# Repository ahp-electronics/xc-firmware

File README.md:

# AHP XC Quantum correlators firmware 

#### This repository contains code of the XC series multichannel multi-order cross-correlators

You'll find board and device specific files into the boards/ folder, device files contain some custom parameters that can characterize the device:

```
parameter PLL_FREQUENCY = 400000000;	//The pll frequency
parameter CLK_FREQUENCY = 10000000;	//The crystal frequency
parameter SIN_FREQUENCY = 50;		//The internal optional PSU frequency
parameter MUX_LINES = 1;		//Muxer lines
parameter NUM_LINES = 8;		//Lines per each Muxer line
parameter DELAY_SIZE = 2048;		//If 4 use quadrature sampling, if 0 use single sample quadrature sampling, else the delay FIFO size
parameter LAG_CROSS = 1;		//Lag lines size for live crosscorrelation
parameter LAG_AUTO = 1;			//Lag lines size for live autocorrelation
parameter RESOLUTION = 24;		//Resolution (count capacity) of each correlation/intensity counter
parameter HAS_LEDS = 1;			//Has this device output lines? (power switches or indicator or ramp generators sync?)
parameter HAS_CROSSCORRELATOR = 1;	//Has this device crosscorrelation capability?
parameter HAS_PSU = 0;			//Has this device a software PSU?
parameter HAS_CUMULATIVE_ONLY = 0;	//Has this device not on-edge counting?
parameter BAUD_RATE = 2000000;		//Communication port baud rate
parameter WORD_WIDTH = 1;		//Word width (greater than 1 when using ADC - must be in sync with the ADC ramp gener
parameter BINARY = 0;		//use binary packet transmission instead of ASCII
parameter USE_UART = 1;			//Use UART or SPI communication?
parameter USE_SOFT_CLOCK = 1;			//Limit usage of gated clocks
parameter MAX_ORDER = 2;			//Maximum crosscorrelation order
```

The generated SVF file can be downloaded to the device using urJTAG http://urjtag.org/

The cross-platform driver library: https://github.com/ahp-electronics/libahp-xc

To use the correlator try the GUI: https://github.com/ahp-electronics/xc-gui

The project runs at 10MHz and uses 2 Mbaud/second UART communication with the host initially

Here below is defined the communication protocol:

    0x0d: Set integration parameters: bit 4 => enable capture, bit 5 => use external clock, bit 6 => reset timestamp when enabling capture, bit 7 => extra commands
    0x01: select active line: first byte: bits [7:4] => length of command LSN, second byte: length of command MSN, next bytes: bits [7:4] => active line LSN first
    0x02: led lines: extra commands => nibble indexer, bits [7:4] => power voltage value
    0x03: if extra commands = 1 first byte: bits [7:4] => length of command LSN, second byte: length of command MSN, next bytes: bits [7:4] => cross-correlator order LSN first, if extra commands = 0 baudrate 57600 left-shifted by bits [7:4] 
    0x04: Set voltage: extra commands => nibble indexer, bits [7:4] => power voltage value
    0x08: sampling clock tau =  first two byte: bits [7:4] => length of command LSN first, next bytes: bits [7:4] => value LSN first - if test[5:4] is 0 scan increment, if test[5:4] is 1 scan length if test[5:4] scan start channel if extra commands = 0 autocorrelator, if extra commands = 1 crosscorrelator.
    0x0c: Set tests: extra commands => nibble indexer, bits [7:4] => test lines value - bit 1 => enable autocorrelation scan, bit 2 => enable crosscorrelation scan, bit 3 => BCM encoder on led 0 (pulse XOR by sampling clock), bits [5:4] => indexer of sampling clock tau

The count of pulses and correlation comes with an ASCII packet string ended with a 0x0d character

Each packet starts with a header with payload length indication, it is possible to change some parameters from the code

header

    char 0: Nibble length of input lines hex digits [n0]
    chars +n0: hexadecimal inputs quantity
    char +1: Nibble length of sample size value hex digits [n1]
    chars +n1: hexadecimal sample size value
    char +1: Nibble length of delay channels hex digits [n2]
    chars +n2: hexadecimal delay channels
    char +1: Nibble length of live autocorrelator delay channels hex digits [n3]
    chars +n3: hexadecimal live autocorrelator delay channels
    char +1: Nibble length of live crosscorrelator delay channels hex digits [n4]
    chars +n4: hexadecimal live crosscorrelator delay channels
    chars +2 hexadecimal flags [bits: 0=live autocorrelator, 1=live crosscorrelator, 2=leds available, 3=cross-correlator, 4=Nyquist sampling, 5=Shannon sampling]
    chars +4: hexadecimal value of the clock tau in picoseconds

payload

    chars +lines*(sample size)#: pulses count of each line within the integration time
    chars +lines*2*(sample size)#: autocorrelations real/imaginary count of each line within the packet time
    chars +baselines*2*(sample size/4)#: crosscorrelations real/imaginary count of pulses of each line with others ones within the packet time
    chars +16: 8-byte timestamp of current packet

checksum

    chars +2: 1-byte CRC of packet payload

EOP

    chars +1: carriage return indicates end of packet

The packet time is determined by the baud rate and the packet size, the sampling rate is determined by the clock tau multiplied by the number of mux lines, raised by the clock tau power of two exponent.

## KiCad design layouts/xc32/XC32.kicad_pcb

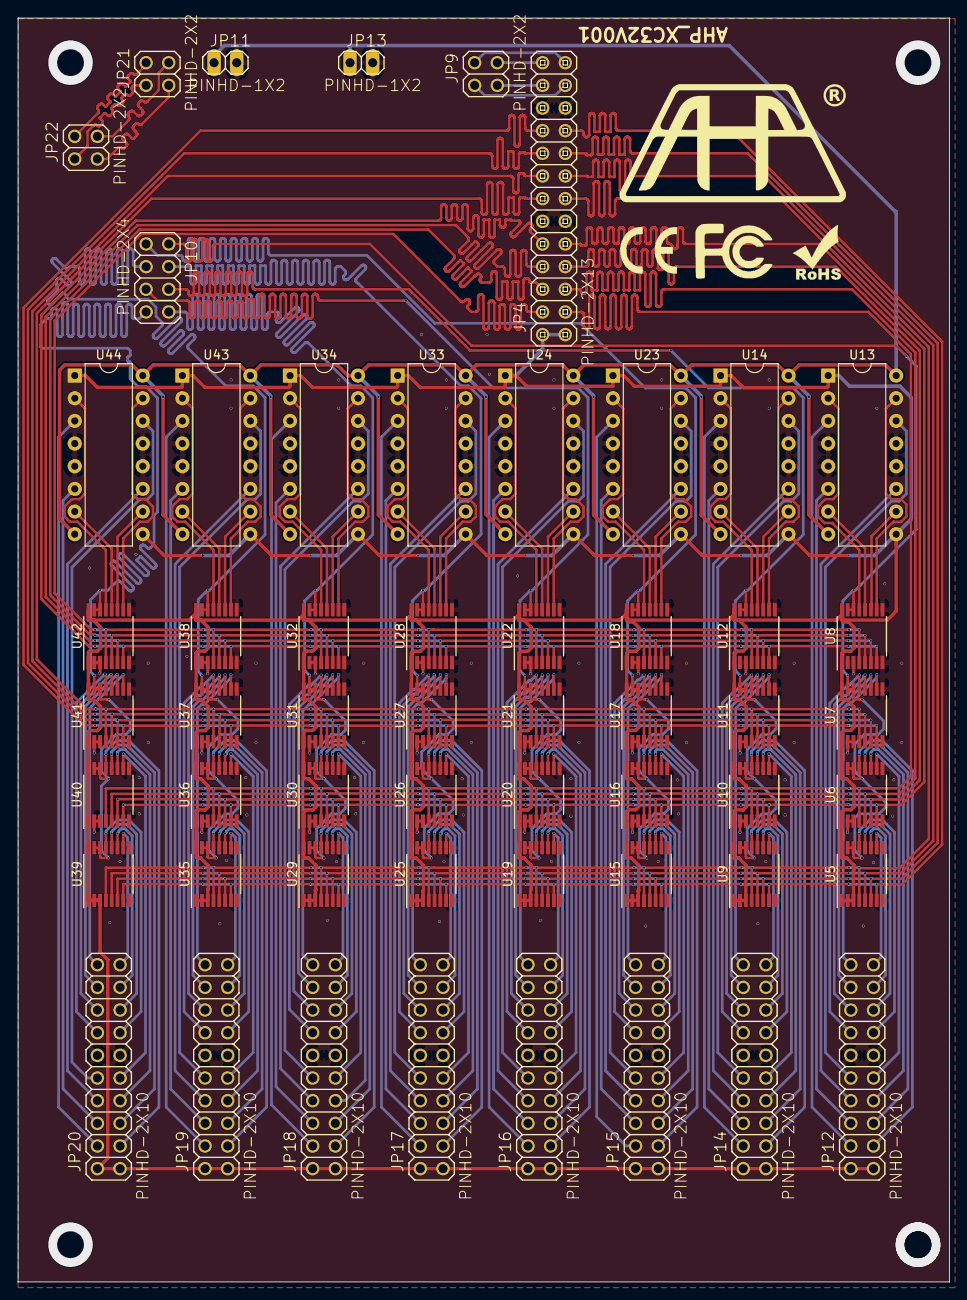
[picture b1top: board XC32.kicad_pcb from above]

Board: 2 copper layers, 104.4 x 141.7 mm, 55 parts (0 on the bottom side), 195 nets.

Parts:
JP4: PINHD-2X13; pinhead-2X13
JP9, JP21, JP22: PINHD-2X2; pinhead-2X02
JP10: PINHD-2X4; pinhead-2X04
JP11, JP13: PINHD-1X2; pinhead-1X02
JP12, JP14, JP15, JP16, JP17, JP18, JP19, JP20: PINHD-2X10; pinhead-2X10
U5, U6, U7, U8, U9, U10, U11, U12, U15, U16, U17, U18, U19, U20, U21, U22, U25, U26, U27, U28, U29, U30, U31, U32, U35, U36, U37, U38, U39, U40, U41, U42: SN74AVC4T245PW; TSSOP-16_4.4x5mm_P0.65mm
U13, U14, U23, U24, U33, U34, U43, U44: L293D; DIP-16_W7.62mm

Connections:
+3V3: JP4.1, JP4.2, JP12.1, JP12.2, JP14.1, JP14.2, JP15.1, JP15.2, JP16.1, JP16.2, JP17.1, JP17.2, JP18.1, JP18.2, JP19.1, JP19.2, JP20.1, JP20.2, U5.1, U5.2, U5.3, U5.16, U6.1, U6.16, U7.1, U7.16, U8.1, U8.16, U9.1, U9.2, U9.3, U9.16, U10.1, U10.16, U11.1, U11.16, U12.1, U12.16, U13.1, U13.9, U14.1, U14.9, U15.1, U15.2, U15.3, U15.16, U16.1, U16.16, U17.1, U17.16, U18.1, U18.16, U19.1, U19.2, U19.3, U19.16, U20.1, U20.16, U21.1, U21.16, U22.1, U22.16, U23.1, U23.9, U24.1, U24.9, U25.1, U25.2, U25.3, U25.16, U26.1, U26.16, U27.1, U27.16, U28.1, U28.16, U29.1, U29.2, U29.3, U29.16, U30.1, U30.16, U31.1, U31.16, U32.1, U32.16, U33.1, U33.9, U34.1, U34.9, U35.1, U35.2, U35.3, U35.16, U36.1, U36.16, U37.1, U37.16, U38.1, U38.16, U39.1, U39.2, U39.3, U39.16, U40.1, U40.16, U41.1, U41.16, U42.1, U42.16, U43.1, U43.9, U44.1, U44.9
+5V: JP11.1, JP13.1, U13.8, U13.16, U14.8, U14.16, U23.8, U23.16, U24.8, U24.16, U33.8, U33.16, U34.8, U34.16, U43.8, U43.16, U44.8, U44.16
/mux1: JP10.2, U5.14, U5.15, U6.14, U6.15, U7.14, U7.15, U8.14, U8.15
/mux2: JP10.1, U15.14, U15.15, U16.14, U16.15, U17.14, U17.15, U18.14, U18.15
/mux3: JP10.4, U25.14, U25.15, U26.14, U26.15, U27.14, U27.15, U28.14, U28.15
/mux4: JP10.3, U35.14, U35.15, U36.14, U36.15, U37.14, U37.15, U38.14, U38.15
/mux5: JP10.6, U9.14, U9.15, U10.14, U10.15, U11.14, U11.15, U12.14, U12.15
/mux6: JP10.5, U19.14, U19.15, U20.14, U20.15, U21.14, U21.15, U22.14, U22.15
/mux7: JP10.8, U29.14, U29.15, U30.14, U30.15, U31.14, U31.15, U32.14, U32.15
/mux8: JP10.7, U39.14, U39.15, U40.14, U40.15, U41.14, U41.15, U42.14, U42.15
/pin1: JP4.3, U6.4, U10.4, U16.4, U20.4, U26.4, U30.4, U36.4, U40.4
/pin2: JP4.4, U8.4, U12.4, U18.4, U22.4, U28.4, U32.4, U38.4, U42.4
/pin3: JP4.5, U6.5, U10.5, U16.5, U20.5, U26.5, U30.5, U36.5, U40.5
/pin4: JP4.6, U8.5, U12.5, U18.5, U22.5, U28.5, U32.5, U38.5, U42.5
/pin5: JP4.7, U6.6, U10.6, U16.6, U20.6, U26.6, U30.6, U36.6, U40.6
/pin6: JP4.8, U8.6, U12.6, U18.6, U22.6, U28.6, U32.6, U38.6, U42.6
/pin7: JP4.9, U6.7, U10.7, U16.7, U20.7, U26.7, U30.7, U36.7, U40.7
/pin8: JP4.10, U8.7, U12.7, U18.7, U22.7, U28.7, U32.7, U38.7, U42.7
/pin9: JP4.13, U5.4, U9.4, U15.4, U19.4, U25.4, U29.4, U35.4, U39.4
/pin10: JP4.14, U7.4, U11.4, U17.4, U21.4, U27.4, U31.4, U37.4, U41.4
/pin11: JP4.15, U5.5, U9.5, U15.5, U19.5, U25.5, U29.5, U35.5, U39.5
/pin12: JP4.16, U7.5, U11.5, U17.5, U21.5, U27.5, U31.5, U37.5, U41.5
/pin13: JP4.17, U5.6, U9.6, U15.6, U19.6, U25.6, U29.6, U35.6, U39.6
/pin14: JP4.18, U7.6, U11.6, U17.6, U21.6, U27.6, U31.6, U37.6, U41.6
/pin15: JP4.19, U5.7, U9.7, U15.7, U19.7, U25.7, U29.7, U35.7, U39.7
/pin16: JP4.20, U7.7, U11.7, U17.7, U21.7, U27.7, U31.7, U37.7, U41.7
GND: JP4.11, JP4.12, JP4.21, JP4.22, JP11.2, JP12.11, JP12.12, JP13.2, JP14.11, JP14.12, JP15.11, JP15.12, JP16.11, JP16.12, JP17.11, JP17.12, JP18.11, JP18.12, JP19.11, JP19.12, JP20.11, JP20.12, U5.8, U5.9, U6.2, U6.3, U6.8, U6.9, U7.2, U7.3, U7.8, U7.9, U8.2, U8.3, U8.8, U8.9, U9.8, U9.9, U10.2, U10.3, U10.8, U10.9, U11.2, U11.3, U11.8, U11.9, U12.2, U12.3, U12.8, U12.9, U13.4, U13.5, U13.12, U13.13, U14.4, U14.5, U14.12, U14.13, U15.8, U15.9, U16.2, U16.3, U16.8, U16.9, U17.2, U17.3, U17.8, U17.9, U18.2, U18.3, U18.8, U18.9, U19.8, U19.9, U20.2, U20.3, U20.8, U20.9, U21.2, U21.3, U21.8, U21.9, U22.2, U22.3, U22.8, U22.9, U23.4, U23.5, U23.12, U23.13, U24.4, U24.5, U24.12, U24.13, U25.8, U25.9, U26.2, U26.3, U26.8, U26.9, U27.2, U27.3, U27.8, U27.9, U28.2, U28.3, U28.8, U28.9, U29.8, U29.9, U30.2, U30.3, U30.8, U30.9, U31.2, U31.3, U31.8, U31.9, U32.2, U32.3, U32.8, U32.9, U33.4, U33.5, U33.12, U33.13, U34.4, U34.5, U34.12, U34.13, U35.8, U35.9, U36.2, U36.3, U36.8, U36.9, U37.2, U37.3, U37.8, U37.9, U38.2, U38.3, U38.8, U38.9, U39.8, U39.9, U40.2, U40.3, U40.8, U40.9, U41.2, U41.3, U41.8, U41.9, U42.2, U42.3, U42.8, U42.9, U43.4, U43.5, U43.12, U43.13, U44.4, U44.5, U44.12, U44.13
unnamed: JP4.23, JP9.2
unnamed: JP4.24, JP9.1
unnamed: JP4.25, JP9.4
unnamed: JP4.26, JP9.3
unnamed: JP12.3, U6.13
unnamed: JP12.4, U13.3
unnamed: JP12.5, U6.12
unnamed: JP12.6, U13.6
unnamed: JP12.7, U6.11
unnamed: JP12.8, U13.11
unnamed: JP12.9, U6.10
unnamed: JP12.10, U13.14
unnamed: JP12.13, U5.13
unnamed: JP12.14, U7.13
unnamed: JP12.15, U5.12
unnamed: JP12.16, U7.12
unnamed: JP12.17, U5.11
unnamed: JP12.18, U7.11
unnamed: JP12.19, U5.10
unnamed: JP12.20, U7.10
unnamed: JP14.3, U10.13
unnamed: JP14.4, U14.3
unnamed: JP14.5, U10.12
unnamed: JP14.6, U14.6
unnamed: JP14.7, U10.11
unnamed: JP14.8, U14.11
unnamed: JP14.9, U10.10
unnamed: JP14.10, U14.14
unnamed: JP14.13, U9.13
unnamed: JP14.14, U11.13
unnamed: JP14.15, U9.12
unnamed: JP14.16, U11.12
unnamed: JP14.17, U9.11
unnamed: JP14.18, U11.11
unnamed: JP14.19, U9.10
unnamed: JP14.20, U11.10
unnamed: JP15.3, U16.13
unnamed: JP15.4, U23.3
unnamed: JP15.5, U16.12
unnamed: JP15.6, U23.6
unnamed: JP15.7, U16.11
unnamed: JP15.8, U23.11
unnamed: JP15.9, U16.10
unnamed: JP15.10, U23.14
unnamed: JP15.13, U15.13
unnamed: JP15.14, U17.13
unnamed: JP15.15, U15.12
unnamed: JP15.16, U17.12
unnamed: JP15.17, U15.11
unnamed: JP15.18, U17.11
unnamed: JP15.19, U15.10
unnamed: JP15.20, U17.10
unnamed: JP16.3, U20.13
unnamed: JP16.4, U24.3
unnamed: JP16.5, U20.12
unnamed: JP16.6, U24.6
unnamed: JP16.7, U20.11
unnamed: JP16.8, U24.11
unnamed: JP16.9, U20.10
unnamed: JP16.10, U24.14
unnamed: JP16.13, U19.13
unnamed: JP16.14, U21.13
unnamed: JP16.15, U19.12
unnamed: JP16.16, U21.12
unnamed: JP16.17, U19.11
unnamed: JP16.18, U21.11
unnamed: JP16.19, U19.10
unnamed: JP16.20, U21.10
unnamed: JP17.3, U26.13
unnamed: JP17.4, U33.3
unnamed: JP17.5, U26.12
unnamed: JP17.6, U33.6
unnamed: JP17.7, U26.11
unnamed: JP17.8, U33.11
unnamed: JP17.9, U26.10
unnamed: JP17.10, U33.14
unnamed: JP17.13, U25.13
unnamed: JP17.14, U27.13
unnamed: JP17.15, U25.12
unnamed: JP17.16, U27.12
unnamed: JP17.17, U25.11
unnamed: JP17.18, U27.11
unnamed: JP17.19, U25.10
unnamed: JP17.20, U27.10
unnamed: JP18.3, U30.13
unnamed: JP18.4, U34.3
unnamed: JP18.5, U30.12
unnamed: JP18.6, U34.6
unnamed: JP18.7, U30.11
unnamed: JP18.8, U34.11
unnamed: JP18.9, U30.10
unnamed: JP18.10, U34.14
unnamed: JP18.13, U29.13
unnamed: JP18.14, U31.13
unnamed: JP18.15, U29.12
unnamed: JP18.16, U31.12
unnamed: JP18.17, U29.11
unnamed: JP18.18, U31.11
unnamed: JP18.19, U29.10
unnamed: JP18.20, U31.10
unnamed: JP19.3, U36.13
unnamed: JP19.4, U43.3
unnamed: JP19.5, U36.12
unnamed: JP19.6, U43.6
unnamed: JP19.7, U36.11
unnamed: JP19.8, U43.11
unnamed: JP19.9, U36.10
unnamed: JP19.10, U43.14
unnamed: JP19.13, U35.13
unnamed: JP19.14, U37.13
unnamed: JP19.15, U35.12
unnamed: JP19.16, U37.12
unnamed: JP19.17, U35.11
unnamed: JP19.18, U37.11
unnamed: JP19.19, U35.10
unnamed: JP19.20, U37.10
unnamed: JP20.3, U40.13
unnamed: JP20.4, U44.3
unnamed: JP20.5, U40.12
unnamed: JP20.6, U44.6
unnamed: JP20.7, U40.11
unnamed: JP20.8, U44.11
unnamed: JP20.9, U40.10
unnamed: JP20.10, U44.14
unnamed: JP20.13, U39.13
unnamed: JP20.14, U41.13
unnamed: JP20.15, U39.12
unnamed: JP20.16, U41.12
unnamed: JP20.17, U39.11
unnamed: JP20.18, U41.11
unnamed: JP20.19, U39.10
unnamed: JP20.20, U41.10
unnamed: JP21.1, JP22.1
unnamed: JP21.2, JP22.2
unnamed: JP21.3, JP22.3
unnamed: JP21.4, JP22.4
unnamed: U12.10, U14.15
unnamed: U12.11, U14.10
unnamed: U12.12, U14.7
unnamed: U12.13, U14.2
unnamed: U8.13, U13.2
unnamed: U8.12, U13.7
unnamed: U8.11, U13.10
unnamed: U8.10, U13.15
unnamed: U18.10, U23.15
unnamed: U18.11, U23.10
unnamed: U18.12, U23.7
unnamed: U18.13, U23.2
unnamed: U22.10, U24.15
unnamed: U22.11, U24.10
unnamed: U22.12, U24.7
unnamed: U22.13, U24.2
unnamed: U28.10, U33.15
unnamed: U28.11, U33.10
unnamed: U28.12, U33.7
unnamed: U28.13, U33.2
unnamed: U32.10, U34.15
unnamed: U32.11, U34.10
unnamed: U32.12, U34.7
unnamed: U32.13, U34.2
unnamed: U38.10, U43.15
unnamed: U38.11, U43.10
unnamed: U38.12, U43.7
unnamed: U38.13, U43.2
unnamed: U42.10, U44.15
unnamed: U42.11, U44.10
unnamed: U42.12, U44.7
unnamed: U42.13, U44.2

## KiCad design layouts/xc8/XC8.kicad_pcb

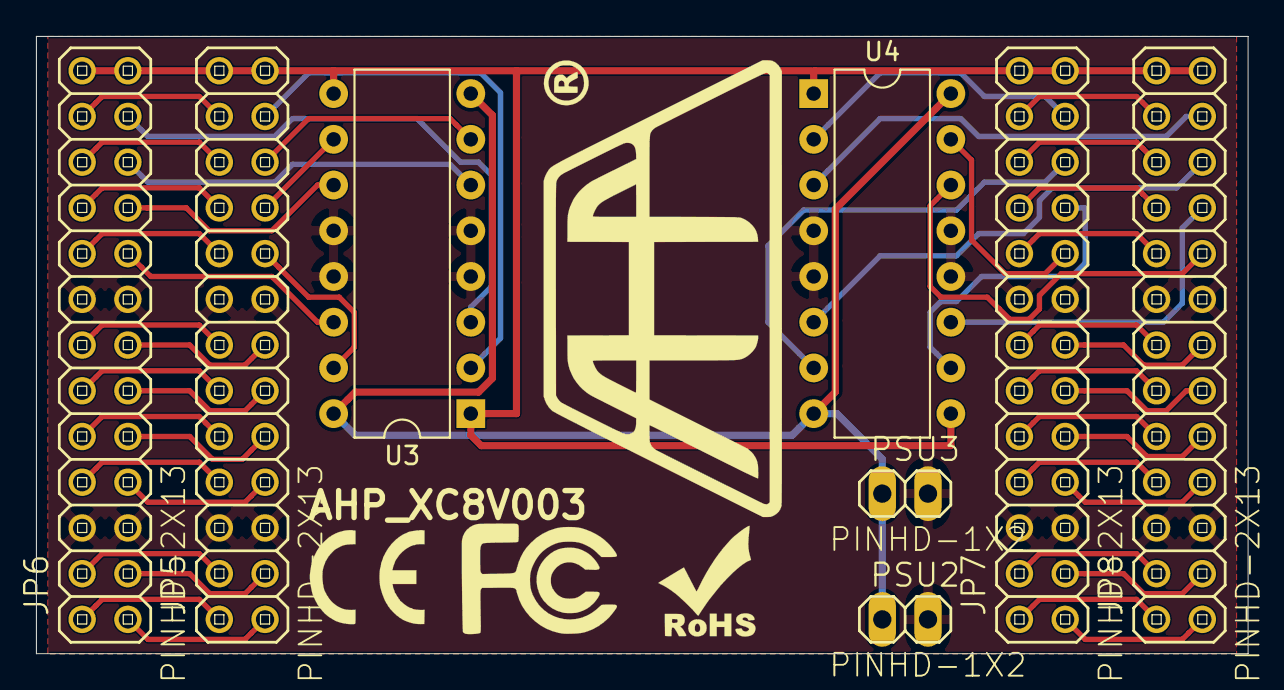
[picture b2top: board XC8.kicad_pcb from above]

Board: 2 copper layers, 67.3 x 34.3 mm, 8 parts (0 on the bottom side), 51 nets.

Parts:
JP5, JP6, JP7, JP8: PINHD-2X13; pinhead-2X13
PSU2, PSU3: PINHD-1X2; pinhead-1X02
U3, U4: L293D; DIP-16_W7.62mm

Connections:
+3V3: JP5.25, JP5.26, JP6.25, JP6.26, JP7.25, JP7.26, JP8.25, JP8.26, U3.1, U3.9, U4.1, U4.9
+5V: PSU2.1, PSU3.1, U3.8, U3.16, U4.8, U4.16
GND: JP5.5, JP5.6, JP5.15, JP5.16, JP6.5, JP6.6, JP6.15, JP6.16, JP7.5, JP7.6, JP7.15, JP7.16, JP8.5, JP8.6, JP8.15, JP8.16, PSU2.2, PSU3.2, U3.4, U3.5, U3.12, U3.13, U4.4, U4.5, U4.12, U4.13
unnamed: JP5.1, JP6.1
unnamed: JP5.2, JP6.2
unnamed: JP5.3, JP6.3
unnamed: JP5.4, JP6.4
unnamed: JP5.7, JP6.7
unnamed: JP5.8, JP6.8
unnamed: JP5.9, JP6.9
unnamed: JP5.10, JP6.10
unnamed: JP5.11, JP6.11
unnamed: JP5.12, JP6.12
unnamed: JP5.13, JP6.13
unnamed: JP5.14, JP6.14
unnamed: JP5.17, U3.15
unnamed: JP5.18, JP6.18
unnamed: JP5.19, U3.10
unnamed: JP5.20, JP6.20
unnamed: JP5.21, U3.7
unnamed: JP5.22, JP6.22
unnamed: JP5.23, U3.2
unnamed: JP5.24, JP6.24
unnamed: JP6.17, U3.14
unnamed: JP6.19, U3.11
unnamed: JP6.21, U3.6
unnamed: JP6.23, U3.3
unnamed: JP7.1, JP8.1
unnamed: JP7.2, JP8.2
unnamed: JP7.3, JP8.3
unnamed: JP7.4, JP8.4
unnamed: JP7.7, JP8.7
unnamed: JP7.8, JP8.8
unnamed: JP7.9, JP8.9
unnamed: JP7.10, JP8.10
unnamed: JP7.11, JP8.11
unnamed: JP7.12, JP8.12
unnamed: JP7.13, JP8.13
unnamed: JP7.14, JP8.14
unnamed: JP7.17, U4.15
unnamed: JP7.18, JP8.18
unnamed: JP7.19, U4.10
unnamed: JP7.20, JP8.20
unnamed: JP7.21, U4.7
unnamed: JP7.22, JP8.22
unnamed: JP7.23, U4.2
unnamed: JP7.24, JP8.24
unnamed: JP8.17, U4.14
unnamed: JP8.19, U4.11
unnamed: JP8.21, U4.6
unnamed: JP8.23, U4.3

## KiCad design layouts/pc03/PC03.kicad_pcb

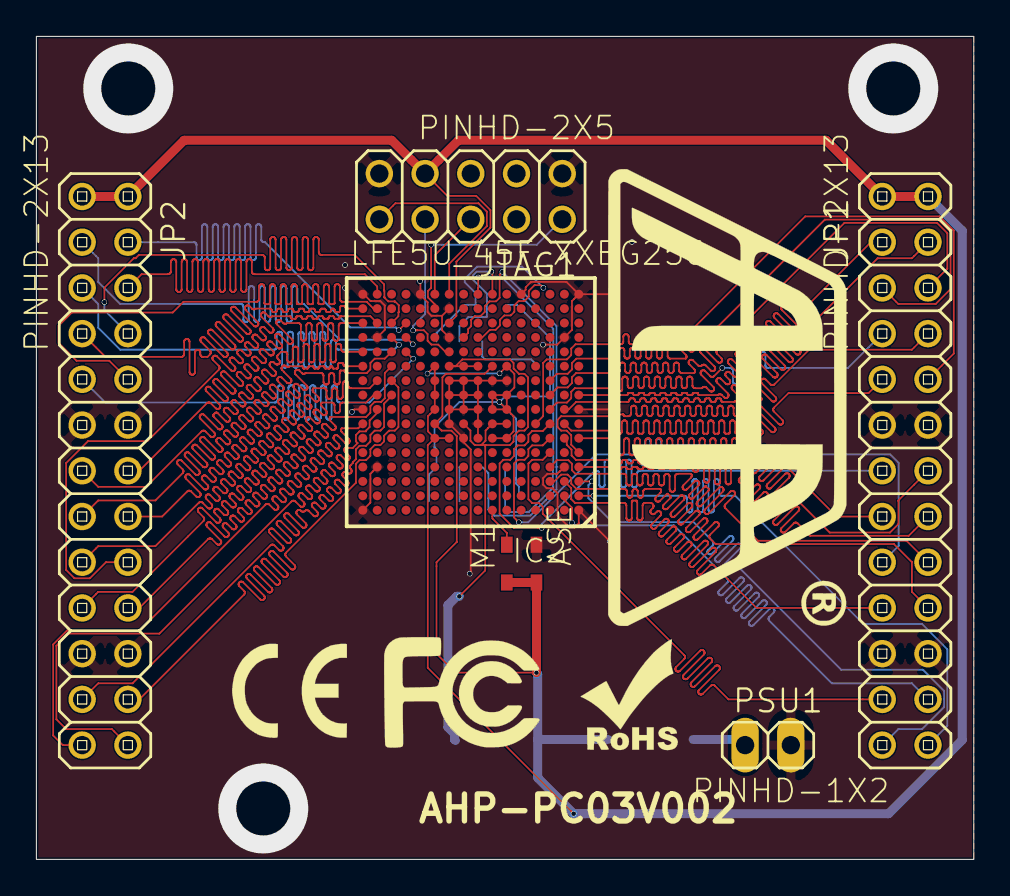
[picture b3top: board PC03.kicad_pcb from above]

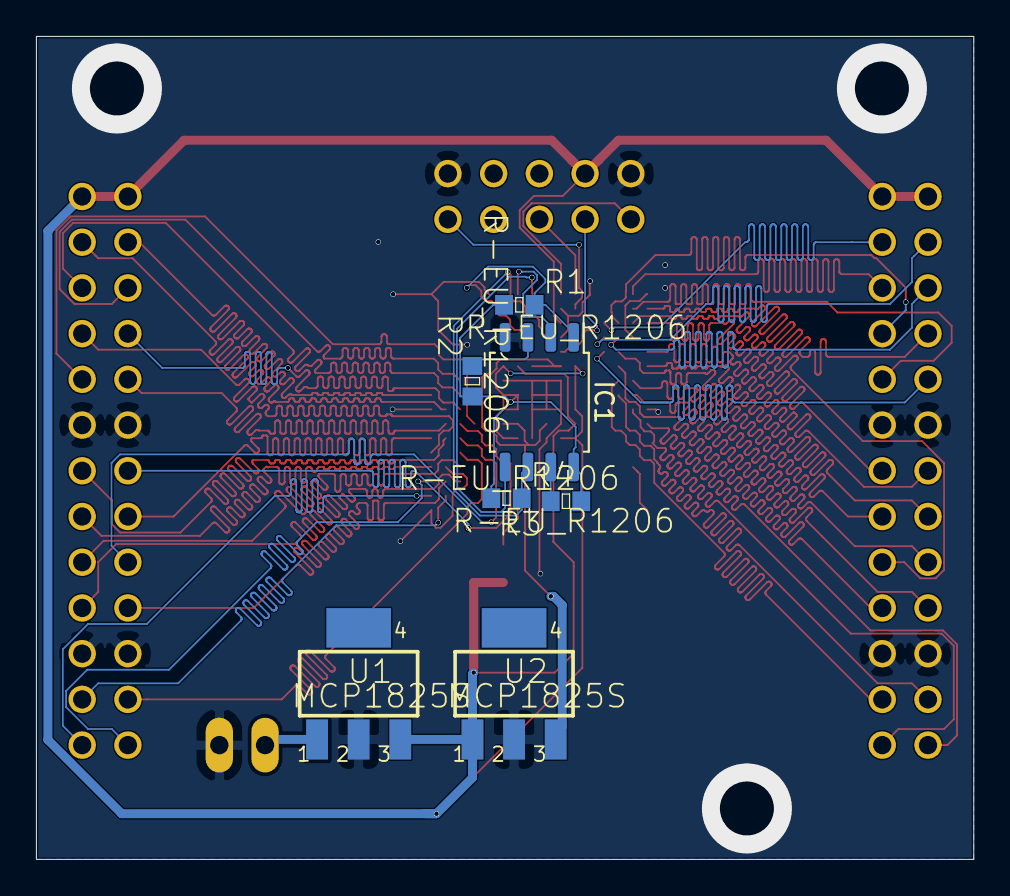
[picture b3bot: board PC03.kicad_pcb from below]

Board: 2 copper layers, 52.1 x 45.7 mm, 13 parts (7 on the bottom side), 55 nets.

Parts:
IC1: DIL8; SOIC-8_5.275x5.275mm_P1.27mm
IC2: LFE5U_45F_XXBG256; lattice-CABGA256
JP1, JP2: PINHD-2X13; pinhead-2X13
JTAG1: PINHD-2X5; pinhead-2X05
M1: ASE
PSU1: PINHD-1X2; pinhead-1X02
R1, R2, R3, R4: R-EU_R1206; resistor-R0603
U1, U2: MCP1825S; linear-SOT223

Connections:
+1V2: IC2.G6, IC2.G7, IC2.G9, IC2.L8, IC2.L9, IC2.L10, U2.3
+3V3: IC1.8, IC2.F6, IC2.F7, IC2.F10, IC2.F11, IC2.G11, IC2.H6, IC2.H7, IC2.H11, IC2.J6, IC2.J7, IC2.J11, IC2.K11, IC2.L6, IC2.L7, IC2.L11, JP1.1, JP1.2, JP2.1, JP2.2, JTAG1.7, M1.1, M1.4, R1.1, R2.1, R3.1, R4.1, U1.3, U2.1
GND: IC1.4, IC2.A1, IC2.A16, IC2.D2, IC2.D15, IC2.F8, IC2.F9, IC2.G8, IC2.G10, IC2.H1, IC2.H8, IC2.H9, IC2.H10, IC2.H16, IC2.J8, IC2.J9, IC2.J10, IC2.K6, IC2.K7, IC2.K8, IC2.K9, IC2.K10, IC2.N2, IC2.N10, IC2.N15, IC2.R10, IC2.T1, IC2.T5, IC2.T12, IC2.T16, JP1.11, JP1.12, JP1.21, JP1.22, JP2.11, JP2.12, JP2.21, JP2.22, JTAG1.1, JTAG1.9, M1.2, PSU1.2, U1.2, U2.2
unnamed: IC1.1, IC2.N8, R1.2
unnamed: IC1.2, IC2.T7
unnamed: IC1.3, R2.2
unnamed: IC1.5, IC2.T8
unnamed: IC1.6, IC2.N9, R4.2
unnamed: IC1.7, R3.2
unnamed: IC2.A7, M1.3
unnamed: IC2.B1, JP1.26
unnamed: IC2.B2, JP1.24
unnamed: IC2.C1, JP1.25
unnamed: IC2.C2, JP1.19
unnamed: IC2.C3, JP1.20
unnamed: IC2.D1, JP1.16
unnamed: IC2.D3, JP1.18
unnamed: IC2.E1, JP1.8
unnamed: IC2.E3, JP1.23
unnamed: IC2.F1, JP1.15
unnamed: IC2.F2, JP1.14
unnamed: IC2.F3, JP1.17
unnamed: IC2.G2, JP1.9
unnamed: IC2.G3, JP1.13
unnamed: IC2.G4, JP1.10
unnamed: IC2.G16, JP2.25
unnamed: IC2.H2, JP1.4
unnamed: IC2.H3, JP1.7
unnamed: IC2.H15, JP2.26
unnamed: IC2.J1, JP1.3
unnamed: IC2.J3, JP1.6
unnamed: IC2.J14, JP2.23
unnamed: IC2.J15, JP2.19
unnamed: IC2.K3, JP1.5
unnamed: IC2.K14, JP2.24
unnamed: IC2.K15, JP2.17
unnamed: IC2.L14, JP2.20
unnamed: IC2.L16, JP2.15
unnamed: IC2.M10, JTAG1.8
unnamed: IC2.M13, JP2.9
unnamed: IC2.M14, JP2.16
unnamed: IC2.M16, JP2.13
unnamed: IC2.N13, JP2.3
unnamed: IC2.N14, JP2.5
unnamed: IC2.P13, JP2.4
unnamed: IC2.P14, JP2.8
unnamed: IC2.P15, JP2.18
unnamed: IC2.P16, JP2.14
unnamed: IC2.R11, JTAG1.2
unnamed: IC2.R15, JP2.10
unnamed: IC2.R16, JP2.7
unnamed: IC2.T10, JTAG1.10
unnamed: IC2.T11, JTAG1.6
unnamed: IC2.T15, JP2.6
VCC: PSU1.1, U1.1

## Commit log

2020-09-20 3-bits delay indexer
2020-09-27 expanded clock divider capability
2020-10-23 Triangle PWM indicator
2020-11-08 increase maximum inputs
2020-11-09 reverted to Jittered packet
2020-11-10 multi-spectrograph
2020-11-10 updated license headr
2020-11-28 removed counts from protocol
2020-12-10 added more led flags
2020-12-11 indices wrong in pulse shaping
2021-01-19 added mux controller
2021-01-19 mux line controls led flags
2021-01-19 fixed error in baseline indexer
2021-01-19 single mux line
2021-01-24 Reordered main.v
2021-01-25 Added clock phase lock
2021-01-27 Restyling...
2021-01-27 Fixed conflicts
2021-01-27 Fixed more conflicts
2021-01-27 added .gitignore
2021-01-27 added pc03 layouts
2021-01-27 renamed .xcf files
2021-01-27 Added tests
2021-01-31 added cmd_parser.v
2021-02-09 2048 autocorrelation lines in xc8
2021-02-09 fixes for module main issues
2021-02-10 increased psu frequency
2021-02-26 Added ramp ADC module and multibit correlation
2021-02-26 Fixed issue in ADC sampling
2021-02-26 Updated xc32.v and xc8.v
2021-02-26 Updated xc32.v
2021-02-26 Updated xc8.v
2021-02-26 Added adc.v
2021-03-12 Added AC1 autocorrelator
2021-03-17 added external hardware synchronization lines
2021-03-22 Added xc256 implementation
2021-03-22 First configuration for xc256
2021-03-22 Add XC8 and XC32 layouts
2021-03-22 32MHz pll on XC256
2021-03-29 moved muxing into generate block
2021-03-29 xc8 with 2048 spectral lines
2021-03-30 added Makefile and templates
2021-03-30 removing adc in pulse counters
2021-03-30 removed makefiles
2021-04-08 added Makefile
2021-04-08 removed dedicated xcf
2021-04-08 Makefile targets uppercase ..:|
2021-04-08 fixing errors in Makefile
2021-04-10 Saving current state
2021-04-11 xc8 release 1
2021-04-13 WinBond as flash device
2021-04-17 changed rx/tx behavior
2021-04-17 added xcf files
2021-04-18 retyping correlation scan
2021-04-18 removed old .xcf files
2021-04-25 XC32 cumulative only
2021-04-27 Added SPI option
2021-04-27 XC8 production
2021-05-28 pulsing external output lines
2021-06-03 Added test svf generation
2021-06-03 Added programming tools
2021-06-07 Added desktop lib and gui modules
2021-07-25 Added Diamond suite
2021-07-30 add build tools
2021-08-02 Updated flash.sh
2021-08-03 Added timestamp at end of frame
2021-10-27 Add checksum at end of packet
2021-12-19 First tests with complex correlations
2021-12-21 Working beta, possible misconception in phasing
2021-12-22 Short tests successful, ready to merge
2021-12-22 autocorrelations start from 0 index
2021-12-29 Added extra commands
2022-01-17 Complex pairs and new license
2022-01-22 Updated Makefile
2022-01-25 Changed license type
2022-02-03 Add AC8
2022-02-04 Add xc32
2022-02-06 Updated flash.sh and Makefile
2022-02-10 Updated flash.sh Makefile and board xcf files
2022-02-11 Adding boards xcf files
2022-02-24 Updated pinout
2022-02-24 Add flash database
2022-02-24 Add CITATION.cff
2022-02-27 Add vendors to flash database
2022-03-15 correct sizes when writing
2022-03-20 Update submodules
2022-03-20 Add BSDL
2022-04-30 edge clock in dff
2022-05-01 Minus 1 at end of scan
2022-05-03 draft of linear scan
2022-05-05 Add scan stepping
2022-05-09 soft clock in counters
2022-05-09 Generate SVF after compilation
2022-05-09 XC32 28 bits sampling capacity
2022-05-09 sampling clocks used by counters
2022-05-09 20bits capacity AC1
2022-05-09 256 channels in AC1
2022-05-11 Add jtag library
2022-05-12 XC32 24 bits
2022-05-13 soft clock option in counters only
2022-05-13 revert to old main.v
2022-05-13 software clock in fifos only
2022-05-13 8bit capacity xc32
2022-05-13 Filter first sample
2022-05-16 xc32 12bits without leds
2022-05-16 xc32 28bits without leds
2022-05-16 xc32 24bits without leds
2022-05-20 Trying XC32 leds enabled
2022-05-20 Invert pulse even if leds are not enabled
2022-05-21 Wrong setting in XC32
2022-05-29 multi-order crosscorrelator
2022-05-29 Wrong correlators instantiation
2022-06-03 correlator module
2022-06-03 wider range for order iterator
2022-06-04 Remove unused parts in correlator
2022-06-04 Correct arrays size
2022-06-04 Variable correlation order
2022-06-04 Inner iteration block not indexing anymore
2022-06-04 limit max order to num inputs if less inputs than 16
2022-06-04 limit max order to 256
2022-06-04 First tests with correlation order greater than 2
2022-06-04 crosscorrelator module
2022-06-04 Corrected syntax on IDE
2022-06-04 Corrected syntax on IDE - part 2
2022-06-04 Corrected syntax on IDE - part 3
2022-06-05 too many iteration loops
2022-06-05 Corrected syntax on IDE - part 4
2022-06-05 Corrected syntax on IDE - part 5
2022-06-05 Maximum correlation order until number of lines
2022-06-05 Maximum order set to 4
2022-06-05 Maximum order set to 2 in XC32
2022-06-05 Add lag in crosscorrelator FIFO
2022-06-05 inverting quadrature sampling for XC32
2022-06-05 typo in overflow bounds
2022-06-05 inverse indexing in crosscorrelator
2022-06-06 Fixed crosscorrelation indexing
2022-06-06 Add edge-detect in crosscorrelator module
2022-06-07 generate indexing
2022-06-08 Still working on indexing
2022-06-10 working on edge detection in crosscorrelator
2022-08-16 updated correlator.v
2022-08-18 Update Makefile
2022-08-23 Limit correlation counts
2022-08-23 Verify written file
2022-08-30 Set order as baudrate extra command
2022-08-30 Fixed erase script
2022-08-31 Iteration on _c in correlator.v
2022-08-31 Version 2.3
2022-09-16 8bit test lines
2022-10-03 Changed baseline ordering
2022-10-03 Wrong indexing in crosscorrelator
2022-10-03 Wrong indexing in crosscorrelator.v
2022-10-05 wrong indexing
2022-10-05 on-edge if leds[4] is 0
2022-10-10 fixed autocorrelation scan
2022-10-11 on-edge autocorrelator and counter
2022-10-12 On-edge differential/multiplicative multi-order cross-correlator
2022-10-12 Update XC32
2022-10-15 Use power of two inputs quantities
2022-11-14 Fixed correlation loop
2022-12-07 24bit XC32
2022-12-07 Add autocorrelator.v and crosscorrelator.v
2022-12-09 Program test only
2022-12-09 Updated crosscorrelator.v
2022-12-09 Larger variable to store baseline index
2022-12-22 Version 2.5
2022-12-26 baselines into generated modules
2022-12-27 Changed quadrature sampling
2023-01-09 Use integer variables for iterations in correlator.v
2023-01-10 BCM PLL clock XOR Integration clock
2023-01-15 Updated board template
2023-01-15 Production (#1)
    * Changed quadrature sampling
    * BCM PLL clock XOR Integration clock
    * Updated board template
    * Update Makefile
2023-02-05 0 delaysize for xc8
2023-02-24 Larger delay register for zero-delay versions
2023-02-24 Nyquist sampling for XC8 and XC32
2023-02-27 Single module crosscorrelator
2023-02-27 Update project file
2023-02-27 Update gitignore
2023-03-04 Version 2.7
2023-03-08 Version 2.8
2023-03-18 Updated Nyquist subsampling
2023-03-20 Remove repetition commands
2023-03-20 intclk as tx_done
2023-03-21 Wrong indexing in carry spectrograph
2023-03-23 Limit maximum order in crosscorrelator
2023-03-25 Sequential correlation
2023-03-27 Differential correlation
2023-04-03 SOF before each scan
2023-04-04 Synced SOF with true enable_capture
2023-04-15 XC32 autocorrelator only
2023-04-15 16th order xc16
2023-04-15 Add xc16.v
2023-04-16 Add xc24
2023-05-16 Add XC20
2023-05-16 Add AC32
2023-06-08 Fix blocking issue in main.v
2023-06-20 Add xc variants
2023-07-03 Remove tools directory
2023-07-03 Add tools symlink
2023-07-15 Start channel wrong in cmd_parser
2023-07-15 Add symlink to tools
2023-07-26 24-bit scan
2023-07-29 18-bit scan
2023-08-06 Single quadrature in xc8
2023-08-18 high-order multiplication
2023-09-08 Create LICENSE
2023-09-21 Add LICENSE
2023-09-21 Add README.md
2024-01-28 XC32 crosscorrelator
2024-02-04 24bit nlines
2024-02-05 Input lines limited by header
2024-02-05 Version 3.0
2024-02-05 Production (#2)
    * Add LICENSE
    * Add LICENSE
    * Add README.md
    ---------
2024-02-10 Add xc128 and xc256
2024-02-10 Production (#3)
    * Add LICENSE
    * Add LICENSE
    * Add README.md
    * Add xc128 and xc256
    ---------
2024-02-11 Dynamic header
2024-02-11 Production (#4)
    * Add LICENSE
    * Add LICENSE
    * Add README.md
    * Add xc128 and xc256
    * Dynamic header
    ---------
2024-02-11 Production (#4)
    * Add LICENSE
    * Add LICENSE
    * Add README.md
    * Add xc128 and xc256
    * Dynamic header
    ---------
2024-02-11 Production (#5)
    * Add LICENSE
    * Add LICENSE
    * Add README.md
    * Add xc128 and xc256
    * Dynamic header
    * Production (#4)
2024-02-11 Production (#5)
    * Add LICENSE
    * Add LICENSE
    * Add README.md
    * Add xc128 and xc256
    * Dynamic header
    * Production (#4)
2024-02-11 Fix dynamic header sizes
2024-02-11 Production (#6)
    * Add LICENSE
    * Add LICENSE
    * Add README.md
    * Add xc128 and xc256
    * Dynamic header
    * Production (#4)
2024-02-11 Production (#7)
    * Add LICENSE
    * Add LICENSE
    * Add README.md
    * Add xc128 and xc256
    * Dynamic header
    * Production (#4)
2024-02-11 Normalize header lengths
2024-02-11 Fix merge on main.v
2024-02-12 Nibble normalization of header lengths
2024-02-13 Fix bugs in sequential header
2024-02-13 Fix header misalignment
2024-02-15 Production (#8)
    * Add LICENSE
    * Add LICENSE
    * Add README.md
    * Add xc128 and xc256
    * Dynamic header
    * Production (#4)
2024-02-24 Command set updated for dynamic header
2024-03-08 Production (#9)
    * Add LICENSE
    * Add LICENSE
    * Add README.md
    * Add xc128 and xc256
    * Dynamic header
    * Production (#4)
2024-03-30 Update boards
2024-03-30 Set program frequency to 1MHz
2024-04-01 Add xc30
2024-04-02 limit order in multiplier <correlator.v>
2024-04-08 Add preload.svf
2024-04-11 revert correlator.v
2024-05-12 Use PLL if baud rate is 2Mbps
2024-05-18 Remove single-shot delay spectrograph
2024-05-20 Remove unused declaration CORRELATION_HEAD_TAIL_SIZE
2024-05-28 Default baudrate set to 57600
2024-05-30 External clock on the front panel
2024-06-13 Sampling oscillators command
2024-06-14 Extra commands sets cross-correlator delays
